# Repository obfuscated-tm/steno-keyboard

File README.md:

# Owen's Steno Keyboard Mk. 1
The PCB, firmware, casing, as well as the keycaps are all made by myself, from scratch.  
The PCB schematics and design, CAD step files, and firmware are stored within their retrospective folders.

## Screenshots

* On the bottom-most row, the keys on both sides that are furthest away from the center are the number keys.  
* The two double length keys in the middle (one on each side) is the '*' key.
* The other keys follow standard steno layout.

* The decision to have each switch have their own GPIO port is just for ease of assembly and that there was no reason not to do so.  

## Bill of Materials 
- 4 M3 x 12mm screw
- 4 M3 x 0.5mm nut
- 25 Mechanical switches (Cherry MX)
- 1 Raspberry Pi Pico
- 1 PCB
- 1 Micro USB cable
- 3 3D printed 2.5u Steno keycaps (OR 2u standard keycaps)
- 22 3D printed 1.5u Steno keycaps (OR 1u standard keycaps)
- 1 3D printed enclosure (Optional, 3 parts)  
~210g of filament total for 3D printed parts

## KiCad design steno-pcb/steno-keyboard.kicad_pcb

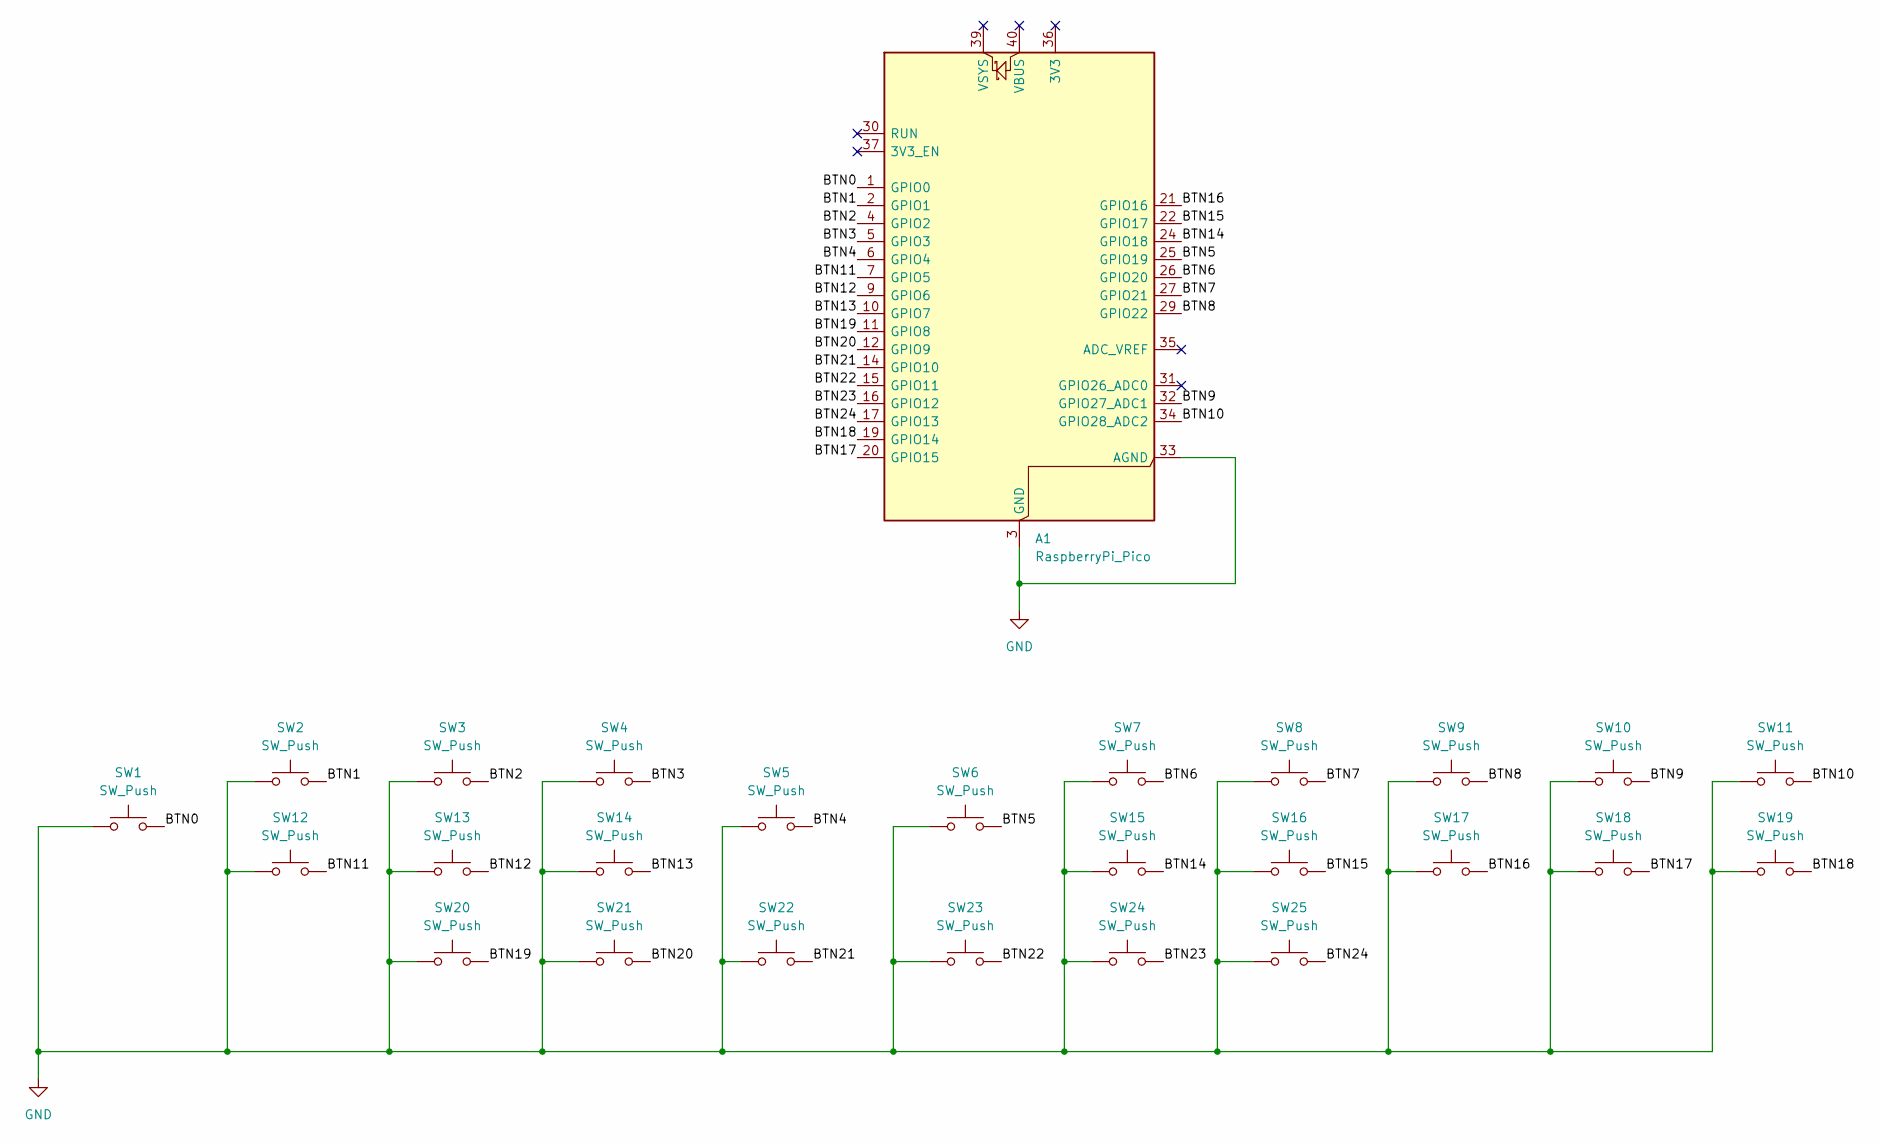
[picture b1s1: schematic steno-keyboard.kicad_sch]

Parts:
A1: RaspberryPi_Pico; RaspberryPi_Pico_Common_Unspecified
SW1, SW2, SW3, SW4, SW5, SW6, SW7, SW8, SW9, SW10, SW11, SW12, SW13, SW14, SW15, SW16, SW17, SW18, SW19, SW20, SW21, SW22, SW23, SW24, SW25: SW_Push; MX-Solderable-1U

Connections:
/BTN0: A1.1 (GPIO0), SW1.2
/BTN1: A1.2 (GPIO1), SW2.2
/BTN2: A1.4 (GPIO2), SW3.2
/BTN3: A1.5 (GPIO3), SW4.2
/BTN4: A1.6 (GPIO4), SW5.2
/BTN5: A1.25 (GPIO19), SW6.2
/BTN6: A1.26 (GPIO20), SW7.2
/BTN7: A1.27 (GPIO21), SW8.2
/BTN8: A1.29 (GPIO22), SW9.2
/BTN9: A1.32 (GPIO27_ADC1), SW10.2
/BTN10: A1.34 (GPIO28_ADC2), SW11.2
/BTN11: A1.7 (GPIO5), SW12.2
/BTN12: A1.9 (GPIO6), SW13.2
/BTN13: A1.10 (GPIO7), SW14.2
/BTN14: A1.24 (GPIO18), SW15.2
/BTN15: A1.22 (GPIO17), SW16.2
/BTN16: A1.21 (GPIO16), SW17.2
/BTN17: A1.20 (GPIO15), SW18.2
/BTN18: A1.19 (GPIO14), SW19.2
/BTN19: A1.11 (GPIO8), SW20.2
/BTN20: A1.12 (GPIO9), SW21.2
/BTN21: A1.14 (GPIO10), SW22.2
/BTN22: A1.15 (GPIO11), SW23.2
/BTN23: A1.16 (GPIO12), SW24.2
/BTN24: A1.17 (GPIO13), SW25.2
GND: A1.3 (GND), A1.8 (GND), A1.13 (GND), A1.18 (GND), A1.23 (GND), A1.28 (GND), A1.33 (AGND), A1.38 (GND), SW1.1, SW2.1, SW3.1, SW4.1, SW5.1, SW6.1, SW7.1, SW8.1, SW9.1, SW10.1, SW11.1, SW12.1, SW13.1, SW14.1, SW15.1, SW16.1, SW17.1, SW18.1, SW19.1, SW20.1, SW21.1, SW22.1, SW23.1, SW24.1, SW25.1

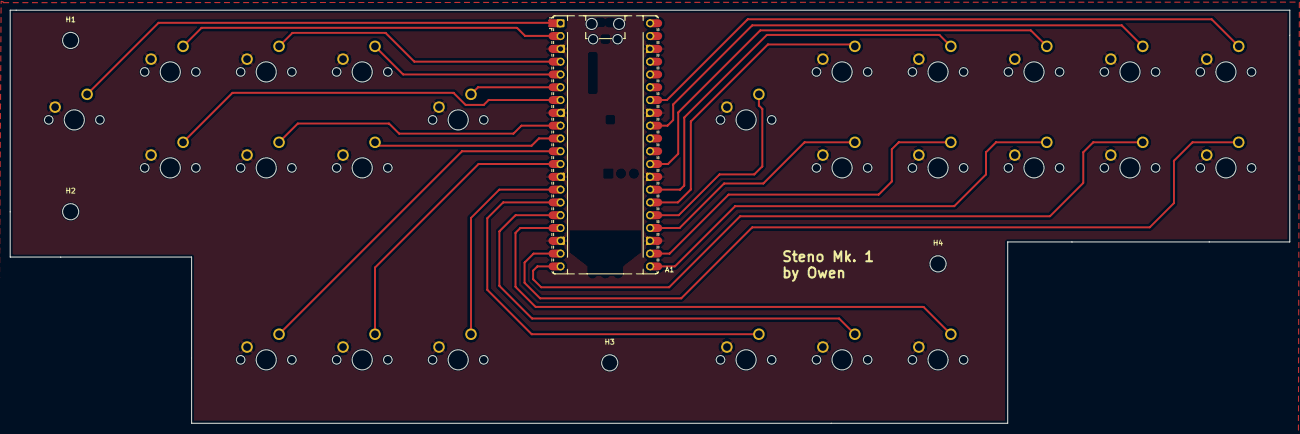
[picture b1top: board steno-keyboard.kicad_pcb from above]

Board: 2 copper layers, 254.0 x 82.0 mm, 30 parts (0 on the bottom side), 26 nets.

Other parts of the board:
H1, H2, H3, H4: MountingHole_3.2mm_M3

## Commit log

2026-03-12 Update steno-keyboard.kicad_sch
    Changed layout from matrix to direct pin into pico
2026-03-12 Updated PCB and footprints
2026-03-12 Organized PCB
2026-03-12 Added traces for PWR
2026-03-13 Finished PCB and rerouted some wires
    Although the layout is messy, it allows for clean routing of the GPIOs
2026-03-13 Small fix to connection BTN17
2026-03-13 Finished PCB
2026-03-13 Organizing files
2026-03-13 Updated PCB's labels
2026-03-13 Updated PCB's labels (KiCad file)
2026-03-15 Started firmware for board in circuit python
2026-03-15 Uses micropy instead of circuit py
    This is treated as a serial device than an HID
2026-03-15 Added .gitignore
    Forgot to put it in when rearranging files
2026-03-19 Update GPIO pins and started PCB'sCAD
    Made the pin numbers the physical pins instead of GPIO.
2026-03-19 Add project description
2026-03-20 Updated 3D model of PCB
    Removed placeholder keycaps and added keyboard switches to all spots (makes it easier to create the models for the keycaps and housing).
2026-03-21 Added keycap STEP files
2026-03-22 Reinforced keycap pin structure
2026-03-22 Slight edit to the pin structure to the 1.5u keycap
    Bumped up the pins' base
2026-04-17 Added keyboard's body CAD files
2026-04-17 Update README with project details and images
    Added additional details about the project, including screenshots and a bill of materials.
2026-04-17 Added render images
2026-04-17 Add Micro USB cable to components list
2026-04-17 Enhance README with key layout descriptions
    Added descriptions for key layout in the screenshots section.
2026-04-17 Fix image tags and layout in README.md
    Updated image tags and corrected formatting in README.
2026-04-17 Update README with GPIO port explanation and image
    Added additional image and explanation regarding GPIO ports.
